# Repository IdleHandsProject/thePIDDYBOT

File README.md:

# thePIDDYBOT
PIDDYBOT is an Open Source Balancing Robot with the aim of teaching PID control.

Check out the Video:

Do not populate F1 or D6

**I somehow lost the original EagleCAD files for the PIDDYBOT. I still have the .BRD file, but no schem. I have plans to update the design with the SAMD21 instead of the Atmel, and it will be done in KiCad not Eagle. Stay Tuned**

There is an instructables on building the PIDDYBOT which contains the parts needed:
https://www.instructables.com/id/PIDDYBOT-DIY-Arduino-Balancing-Robot/

The FindChips(BOM):
https://www.findchips.com/org/10-open-hardware/list/46854-the-piddybot-encoders?sort=created&order=desc

HaD.io: https://hackaday.io/project/27330-the-piddybot

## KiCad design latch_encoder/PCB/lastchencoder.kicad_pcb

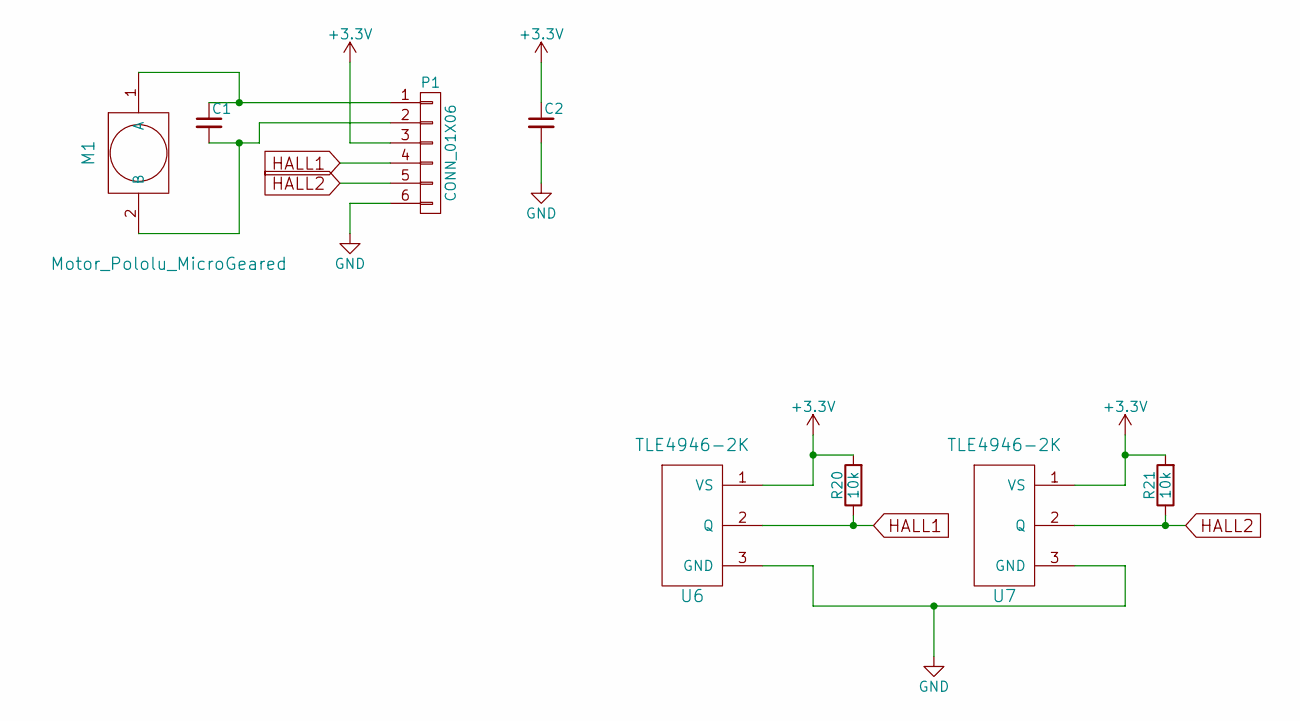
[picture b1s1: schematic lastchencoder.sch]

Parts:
C1: 3.3nF; C_0402_Hand; Digikey Part No. 1276-1549-1-ND
C2: 0.1uF; C_0402_Hand; Digikey Part No. 490-6328-1-ND
M1: Motor_Pololu_MicroGeared; motor_pololu_microgeared
P1: CONN_01X06; Connectors_JST_SM06B-SRSS-TB
R20, R21: 10k; R_0402_Hand; Digikey Part No. 311-10KJRCT-ND
U6, U7: TLE4946-2K; SOT23; Digikey Part No. TLE49462KHTSA1CT-ND

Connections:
+3V3: C2.1, P1.3, R20.2, R21.2, U6.1 (VS), U7.1 (VS)
GND: C2.2, P1.6, U6.3 (GND), U7.3 (GND)
HALL1: P1.4, R20.1, U6.2 (Q)
HALL2: P1.5, R21.1, U7.2 (Q)
unnamed: C1.1, M1.1 (A), P1.1
unnamed: C1.2, M1.2 (B), P1.2

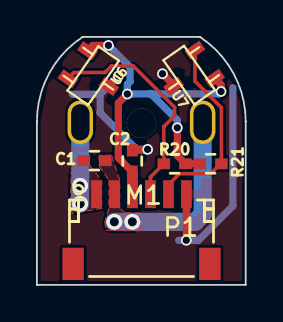
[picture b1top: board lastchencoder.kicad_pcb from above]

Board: 2 copper layers, 11.6 x 13.8 mm, 8 parts (0 on the bottom side), 6 nets.

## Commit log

2017-09-17 added firmware
2017-09-17 updated body
2017-09-21 Program Improvements(EEPROM etc.)
2017-09-21 added updated BOM
2017-09-21 renamed
2017-09-21 Quick Start Guide
2017-10-08 Added SCH file, updated firmware
2017-10-09 Added function demo
